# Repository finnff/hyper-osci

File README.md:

# HYPEROSCI

**4 battery-powered, WiFi-synchronized oscilloscopes drawing vector graphics in X/Y mode — for live performance.**

Each of the 4 slave units drives one analog oscilloscope with a stereo audio signal (L = X, R = Y). A central controller (Arduino UNO-Q running Debian) renders osci-render-style vectors as 48 kHz audio and streams it over its own WiFi access point. When the network is gone, every slave falls back within ~6 s to the proven standalone mode: its own microphone drives the scope as an audio-reactive Lissajous visualizer. No laptop on stage, no venue WiFi needed.

## Architecture

```
                     phone browser (web UI, http://192.168.50.1:8080)
                                      │
                                      ▼
        ┌─────────────────────────────────────────────┐
        │        Arduino UNO-Q  (Debian, QRB2210)     │
        │  renderer ─▶ streamer ─▶ WiFi AP (2.4 GHz)  │
        │        SSID HYPEROSCI_AP · 192.168.50.1     │
        └───────┬─────────┬──────────┬─────────┬──────┘
        UDP :5000 audio (unicast ×4) · :5001 sync/cmd · :5002 status
                │         │          │         │
                ▼         ▼          ▼         ▼
          ┌─────────┐ ┌─────────┐ ┌─────────┐ ┌─────────┐
          │ slave 1 │ │ slave 2 │ │ slave 3 │ │ slave 4 │   ESP32-C3 SuperMini
          │         │ │         │ │         │ │         │   + PCM5102A I2S DAC
          │ mic ────┤ │ mic ────┤ │ mic ────┤ │ mic ────┤   + MAX4466 mic (fallback)
          └────┬────┘ └────┬────┘ └────┬────┘ └────┬────┘   + LiPo/TP4056, custom THT carrier PCB
           X/Y ▼       X/Y ▼       X/Y ▼       X/Y ▼
          ┌─────────┐ ┌─────────┐ ┌─────────┐ ┌─────────┐
          │ scope 1 │ │ scope 2 │ │ scope 3 │ │ scope 4 │   analog scopes in X/Y mode
          └─────────┘ └─────────┘ └─────────┘ └─────────┘
```

Sync target ±5 ms via 500 ms beacons; the stream deliberately runs ~450 ms ahead of playback (512 ms slave jitter buffer) to ride out the UNO-Q radio's periodic ~300 ms stalls — latency is irrelevant for scope art, only slave-to-slave sync matters; stream loss > 1 s → automatic local-mic fallback.

## Documentation

**[docs/DESIGN.md](docs/DESIGN.md) is the single source of truth.** Where any other doc disagrees, DESIGN.md wins.

| Doc | What it is |
|-----|------------|
| [docs/DESIGN.md](docs/DESIGN.md) | Canonical decisions: pin map, modules, modes, power, network (LAW) |
| [docs/PLAN.md](docs/PLAN.md) | 5-week execution plan (Jul 17 → Aug 21), critical path, risks, shopping list |
| [docs/protocol.md](docs/protocol.md) | Normative wire protocol (with [src/esp32-slave/include/protocol.h](src/esp32-slave/include/protocol.h)) |
| [docs/hardware/wiring.md](docs/hardware/wiring.md) | Complete hookup guide + bring-up checklist (breadboard now, PCB later) |
| [docs/hardware/pcb.md](docs/hardware/pcb.md) | Carrier PCB: full BOM, power path, layout notes |
| [docs/hardware/power-budget.md](docs/hardware/power-budget.md) | Current draw, battery life, low-battery policy derivation |
| [docs/hardware/bench-capture.md](docs/hardware/bench-capture.md) | Checking slave output without a scope: logic analyzer / spare-MCU capture options, closed agent loop |
| [docs/firmware/esp32-architecture.md](docs/firmware/esp32-architecture.md) | Slave firmware architecture (tasks, drivers, buffers) |
| [docs/osci-render-feature-port-feasibility.md](docs/osci-render-feature-port-feasibility.md) | What else is worth porting from osci-render (fonts, SVG, effects), measured on the board — and the 6 bugs found while looking, all now fixed (§1) |
| [docs/performance-heat-analysis.md](docs/performance-heat-analysis.md) | Why the slave runs hot and why streaming dropped (2026-07-18), with the prioritized fix plan |
| [docs/hardware/pcb-review-findings.md](docs/hardware/pcb-review-findings.md) | 2026-07-26 adversarial design review of the carrier's §4 power path (findings + verdicts) |
| [docs/research/](docs/research/) | Historical planning docs — superseded where they conflict with DESIGN.md |

Research index: [v3.md](docs/research/v3.md) (feasibility) · [v3.1-requirements.md](docs/research/v3.1-requirements.md) (confirmed requirements) · [v3.2-dual-dac.md](docs/research/v3.2-dual-dac.md) (DAC selection) · [UNO-Q_controller.md](docs/research/UNO-Q_controller.md) (controller architecture — note: its whole software stack is illustrative and was NOT built as described: no FastAPI/WebSocket/hostapd, and its 5 GHz AP config is wrong — see DESIGN.md §2 and src/unoq-controller/README.md for what exists) · [esp32-c3-vs-s3.md](docs/research/esp32-c3-vs-s3.md) · [arduino-uno-r4-option.md](docs/research/arduino-uno-r4-option.md) · [README-original.md](docs/research/README-original.md)

## Hardware summary

Per slave (modules socketed on a custom ~70 × 50 mm through-hole carrier PCB — see [docs/hardware/pcb.md](docs/hardware/pcb.md)):

| Module | Role |
|--------|------|
| ESP32-C3 SuperMini | MCU, WiFi, I2S master |
| GY-PCM5102A | 24-bit stereo I2S DAC → scope X/Y via 2× RCA pads (X = L, Y = R), ground-centered DC-coupled |
| MAX4466 | electret mic (on a ~10 cm pigtail) for fallback/hybrid mode |
| TP4056 (USB-C, with protection) + EEMB LP103454 LiPo 3.7 V 2000 mAh | power (~13 h NETWORK / ~30 h LOCAL) |

Scope output is 2× RCA flying-lead pads (X = DAC L, Y = DAC R, series R fitted as 0 Ω links — the DAC module already carries ~470 Ω of its own) driving reused ~50 cm RCA cables into each scope's existing BNC→RCA adapter — no BNC/TRS on our board. Enclosure: 3D-printed case (4× M3 mounts), LiPo mounted off-PCB.

Controls per unit: power switch, mode button (NETWORK / LOCAL / HYBRID), filter-cutoff pot, 2 status LEDs. Controller: 1× Arduino UNO-Q (4 GB, Debian). Pin map and all constants: [src/esp32-slave/include/config.h](src/esp32-slave/include/config.h) — **canonical, do not improvise**.

## Status (2026-07-28)

- [x] Research + feasibility (docs/research/)
- [x] Design locked ([docs/DESIGN.md](docs/DESIGN.md))
- [x] Hardware modules owned/ordered (SuperMinis, DACs, mics, chargers, UNO-Q — arrived, Debian 13 trixie aarch64)
- [x] Slave firmware (`src/esp32-slave/`): full audio/network/mode stack — AsyncUDP audio RX, 512 ms jitter buffer + concealment, local mic/pattern renderers, console; unit #1 on breadboard streams end-to-end
- [x] UNO-Q controller app **deployed** (`hyperosci-controller` systemd service): streamer + web UI + patterns/Hershey-font text (accents composed from the face's own strokes)/effects/presets — [src/unoq-controller/README.md](src/unoq-controller/README.md). osci-render was built for aarch64 but deliberately **not** integrated (no headless entry point — [docs/text-rendering-findings.md](docs/text-rendering-findings.md))
- [x] Six controller bugs found by the feature-port study fixed and deployed 2026-07-22, including the one that had the daemon beaconing out of the USB tether instead of the AP — slave 121 now receives audio ([docs/…feasibility.md §1](docs/osci-render-feature-port-feasibility.md))
- [x] Boots unattended 2026-07-22: `hyperosci-ap` now autoconnects (it never did — that, not the controller, was the real "no slaves discovered yet…"), the USB tether holds a fixed `10.42.0.5` alongside DHCP, and the dashboard names the AP-down case instead of showing an empty list. Cold boot to streaming: 18 s ([src/unoq-controller/STATUS.md](src/unoq-controller/STATUS.md))
- [x] Survives a power cut with no laptop 2026-07-22: the live pattern persists to `~/hype_state.json` and is restored before the first audio block, presets keep one generation of undo, and a root `hyperosci-netwatch` timer re-ups the AP (and bounces it on the documented ath10k wedge). Regression checks in [src/unoq-controller/tests/](src/unoq-controller/tests/) — run them **on the board**
- [x] Carrier PCB designed & **ordered 2026-07-28** — JLCPCB, qty 10, DHL Express (DDP), $45.42 landed, arriving **Aug 5–7** (order gate was ~Aug 1; met three days early — see [docs/PLAN.md](docs/PLAN.md)). ⏳ Production is paused until the production file is confirmed by email. **Routed and gate-clean as of 2026-07-28** — the pre-fab DFM pass moved copper and killed router seed 11; a 16-variant re-sweep found exactly one clean result (**seed 33**, now the default) and the board is 1343 segments / 48 GND vias / 0 unconnected / 0 DRC violations, with the width tables regenerated from the routed copper. **Nothing gates the plot any more:** SW1 was the last item and it closed 2026-07-28 off the SS12D00 drawing — 2.5 mm pitch (neither value the footprint was drawn for, and 0.05 mm off the centre of the slot's window), body 8.5 × 3.7 mm on the pin centreline, no layout change. **The fab package is plotted and committed** to [`hw/carrier/fab/`](hw/carrier/fab/); `tools/plot_fab.py` regenerates it and refuses to write the zip unless the board still passes. Detail: [`hw/carrier/layout-notes.md`](hw/carrier/layout-notes.md)
- [ ] 4-slave sync demo (slaves 2–4 not yet on breadboards; 3 built slaves need reflashing for the lost-packets counter)
- [ ] Assembly + venue rehearsal (show 2026-08-21)

## Repository layout

```
docs/                 all documentation (DESIGN.md = canon)
  research/           original v3 planning docs (historical)
  hardware/           wiring, power budget, PCB
  firmware/           firmware architecture
  protocol.md         normative wire protocol
  PLAN.md             5-week execution plan
src/esp32-slave/      PlatformIO project — slave firmware
src/unoq-controller/  UNO-Q controller app (streamer + renderer + web UI, deployed)
hw/carrier/           KiCad carrier PCB — generated end-to-end by tools/*.py
```

The repo root also carries two gitignored third-party binaries: `arduino-flasher-cli` (UNO-Q Debian flasher) and `osci-render-premium-linux.zip` (x86-64 only — does not run on the aarch64 UNO-Q; kept for desktop reference. The controller renders natively instead, see [docs/text-rendering-findings.md](docs/text-rendering-findings.md)).

## Quickstart

Slave firmware build/flash instructions: **[src/esp32-slave/README.md](src/esp32-slave/README.md)** (PlatformIO + pioarduino platform, USB-C CDC console).

One rule worth repeating from DESIGN.md §9: **during breadboard bring-up, never plug in USB-C while the battery power switch is ON** — SuperMini clones tie VBUS to the 5 V pin (meter-confirmed 2026-07-18) and would back-feed the battery. Flash with the switch OFF. The carrier PCB's load-sharing power path is *intended* to remove this rule, but design review (2026-07-26) found the SuperMini-side detection unreliable against a sagging laptop port — so treat the rule as permanent until `docs/hardware/pcb.md` §4.4 passes on an assembled board.

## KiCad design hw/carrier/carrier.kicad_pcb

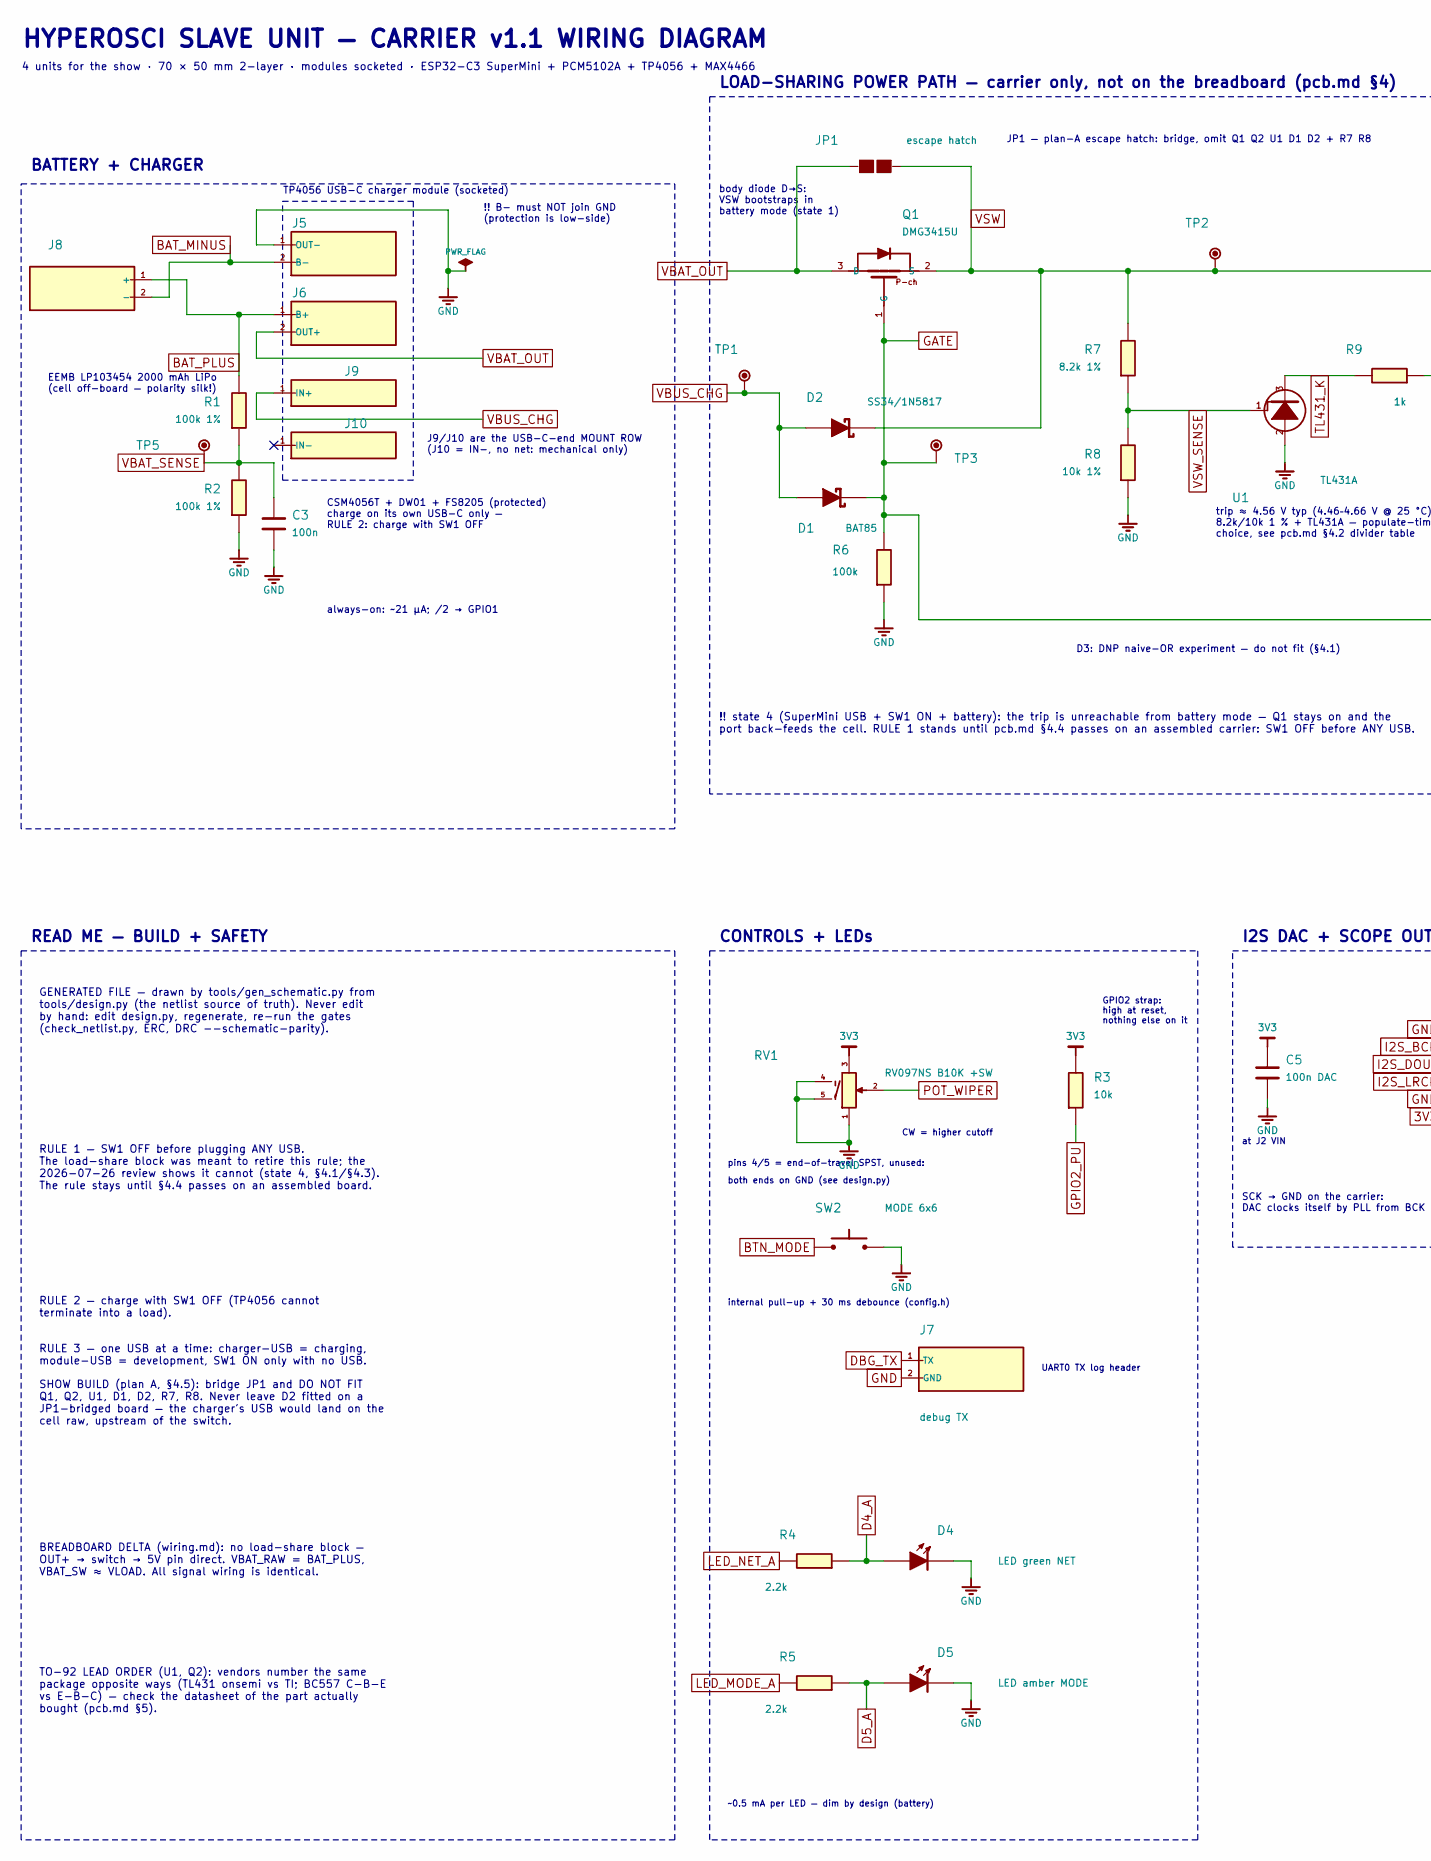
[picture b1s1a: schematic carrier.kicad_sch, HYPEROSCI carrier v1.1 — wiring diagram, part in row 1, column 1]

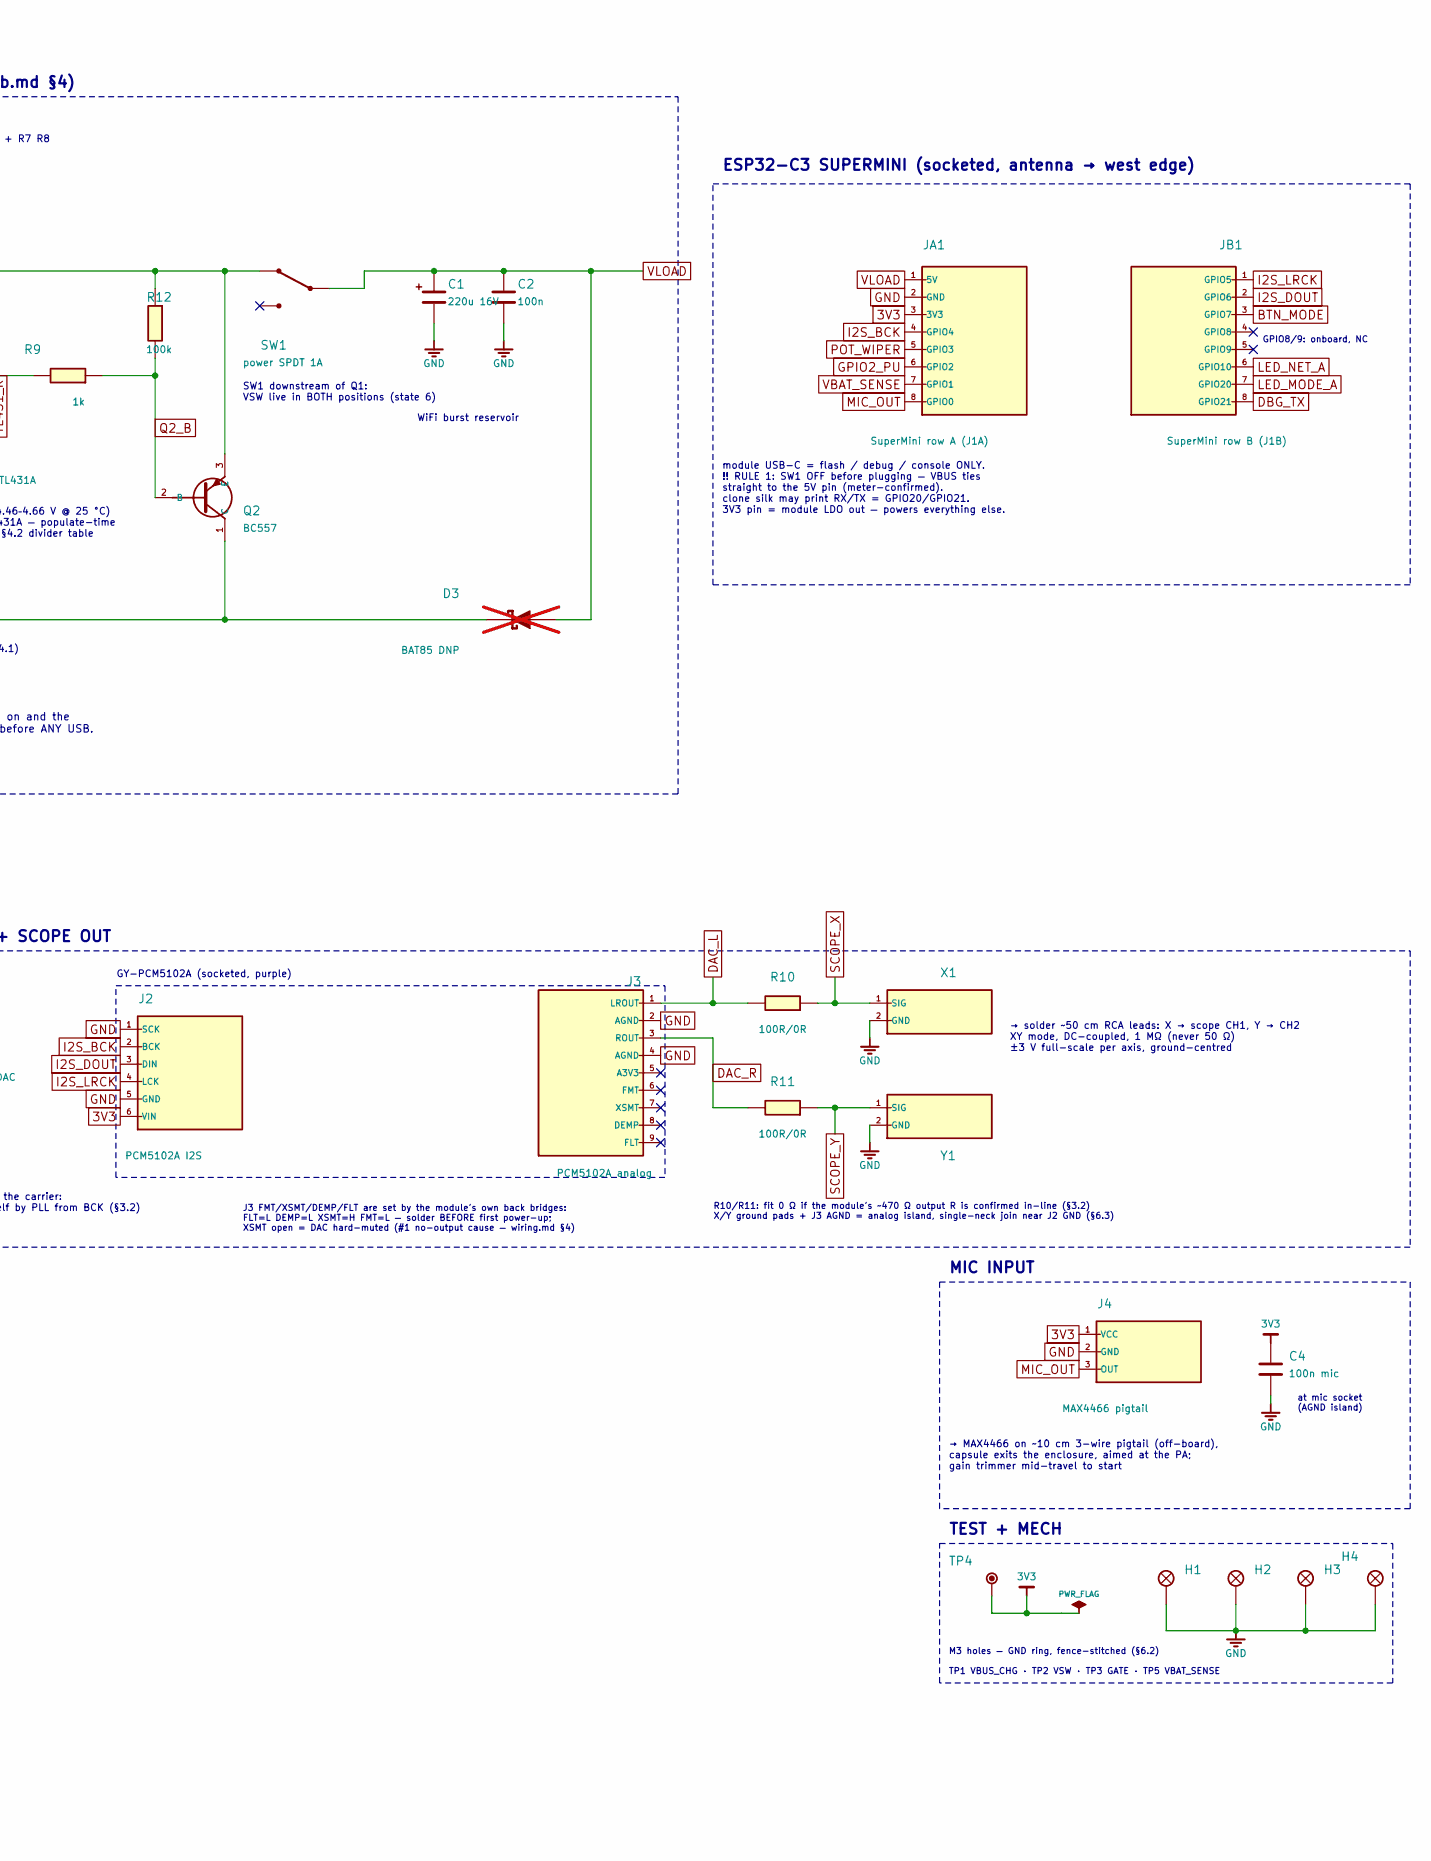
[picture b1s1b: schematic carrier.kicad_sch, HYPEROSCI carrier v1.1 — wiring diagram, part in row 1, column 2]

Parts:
C1: 220u 16V; CP_Radial_D6.3mm_P2.50mm
C2, C3: 100n; C_Disc_D5.0mm_W2.5mm_P2.50mm
C4: 100n mic; C_Disc_D5.0mm_W2.5mm_P2.50mm
C5: 100n DAC; C_Disc_D5.0mm_W2.5mm_P2.50mm
D1: BAT85; D_DO-35_SOD27_P7.62mm_Horizontal
D2: SS34/1N5817; D_Dual_SMA_DO41
D3: BAT85 DNP; D_DO-35_SOD27_P7.62mm_Horizontal; not fitted
D4: LED green NET; LED_D3.0mm
D5: LED amber MODE; LED_D3.0mm
H1, H2, H3, H4: M3; MountingHole_3.2mm_M3_Pad
J2: PCM5102A I2S; PinSocket_1x06_P2.54mm_Vertical
J3: PCM5102A analog; PinSocket_1x09_P2.54mm_Vertical
J4: MAX4466 pigtail; PinSocket_1x03_P2.54mm_Vertical
J5: TP4056 OUT-/B-; TP4056_Pads_OUTminus_Bminus
J6: TP4056 B+/OUT+; TP4056_Pads_Bplus_OUTplus
J7: debug TX; PinHeader_1x02_P2.54mm_Vertical
J8: LiPo JST-PH; JST_PH_S2B-PH-K_1x02_P2.00mm_Horizontal
J9: TP4056 IN+ / mount (J6b); TP4056_MountPin
J10: TP4056 IN- / mount; TP4056_MountPin
JA1: SuperMini row A (J1A); PinSocket_1x08_P2.54mm_Vertical
JB1: SuperMini row B (J1B); PinSocket_1x08_P2.54mm_Vertical
JP1: escape hatch; SolderJumper_P2.54
Q1: DMG3415U; SOT-23_Handsoldering
Q2: BC557; TO-92_Inline_Wide
R1, R2: 100k 1%; R_Axial_DIN0207_L6.3mm_D2.5mm_P2.54mm_Vertical
R3: 10k; R_Axial_DIN0207_L6.3mm_D2.5mm_P10.16mm_Horizontal
R4, R5: 2.2k; R_Axial_DIN0207_L6.3mm_D2.5mm_P2.54mm_Vertical
R6, R12: 100k; R_Axial_DIN0207_L6.3mm_D2.5mm_P2.54mm_Vertical
R7: 8.2k 1%; R_Axial_DIN0207_L6.3mm_D2.5mm_P2.54mm_Vertical
R8: 10k 1%; R_Axial_DIN0207_L6.3mm_D2.5mm_P2.54mm_Vertical
R9: 1k; R_Axial_DIN0207_L6.3mm_D2.5mm_P2.54mm_Vertical
R10, R11: 100R/0R; R_Axial_DIN0207_L6.3mm_D2.5mm_P2.54mm_Vertical
RV1: RV097NS B10K +SW; RV097NS_Horizontal_Switch
SW1: power SPDT 1A; SW_Slide_SPDT_DualPitch
SW2: MODE 6x6; SW_PUSH_6mm_H5mm
TP1: VBUS_CHG; TestPoint_Pad_D1.5mm
TP2: VSW; TestPoint_Pad_D1.5mm
TP3: GATE; TestPoint_Pad_D1.5mm
TP4: 3V3; TestPoint_Pad_D1.5mm
TP5: VBAT_SENSE; TestPoint_Pad_D1.5mm
U1: TL431A; TO-92_Inline_Wide
X1: scope X RCA pads; RCA_FlyingLead_Pads
Y1: scope Y RCA pads; RCA_FlyingLead_Pads

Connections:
3V3: C4.1, C5.1, J2.6 (VIN), J4.1 (VCC), JA1.3 (3V3), R3.1, RV1.3 (CW), TP4.1
BAT_MINUS: J5.2 (B-), J8.2 (-)
BAT_PLUS: J6.1 (B+), J8.1 (+), R1.1
BTN_MODE: JB1.3 (GPIO7), SW2.1
D4_A: D4.2 (A), R4.2
D5_A: D5.2 (A), R5.2
DAC_L: J3.1 (LROUT), R10.1
DAC_R: J3.3 (ROUT), R11.1
DBG_TX: J7.1 (TX), JB1.8 (GPIO21)
GATE: D1.1 (K), D3.1 (K), Q1.1 (G), Q2.1 (C), R6.1, TP3.1
GND: C1.2 (-), C2.2, C3.2, C4.2, C5.2, D4.1 (K), D5.1 (K), H1.1, H2.1, H3.1, H4.1, J2.1 (SCK), J2.5 (GND), J3.2 (AGND), J3.4 (AGND), J4.2 (GND), J5.1 (OUT-), J7.2 (GND), JA1.2 (GND), R2.2, R6.2, R8.2, RV1.1 (CCW), RV1.4 (S1), RV1.5 (S2), SW2.2, U1.2 (A), X1.2 (GND), Y1.2 (GND)
GPIO2_PU: JA1.6 (GPIO2), R3.2
I2S_BCK: J2.2 (BCK), JA1.4 (GPIO4)
I2S_DOUT: J2.3 (DIN), JB1.2 (GPIO6)
I2S_LRCK: J2.4 (LCK), JB1.1 (GPIO5)
LED_MODE_A: JB1.7 (GPIO20), R5.1
LED_NET_A: JB1.6 (GPIO10), R4.1
MIC_OUT: J4.3 (OUT), JA1.8 (GPIO0)
POT_WIPER: JA1.5 (GPIO3), RV1.2 (W)
Q2_B: Q2.2 (B), R9.2, R12.1
SCOPE_X: R10.2, X1.1 (SIG)
SCOPE_Y: R11.2, Y1.1 (SIG)
TL431_K: R9.1, U1.3 (K)
VBAT_OUT: J6.2 (OUT+), JP1.1, Q1.3 (D)
VBAT_SENSE: C3.1, JA1.7 (GPIO1), R1.2, R2.1, TP5.1
VBUS_CHG: D1.2 (A), D2.2 (A), J9.1, TP1.1
VLOAD: C1.1 (+), C2.1, D3.2 (A), JA1.1 (5V), SW1.2 (COM)
VSW: D2.1 (K), JP1.2, Q1.2 (S), Q2.3 (E), R7.1, R12.2, SW1.1 (A), TP2.1
VSW_SENSE: R7.2, R8.1, U1.1 (REF)

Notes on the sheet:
BATTERY + CHARGER
TP4056 USB-C charger module (socketed)
J9/J10 are the USB-C-end MOUNT ROW (J10 = IN-, no net: mechanical only)
CSM4056T + DW01 + FS8205 (protected) charge on its own USB-C only — RULE 2: charge with SW1 OFF
EEMB LP103454 2000 mAh LiPo (cell off-board — polarity silk!)
!! B− must NOT join GND (protection is low-side)
always-on: ~21 µA; /2 → GPIO1
LOAD-SHARING POWER PATH — carrier only, not on the breadboard (pcb.md §4)
JP1 — plan-A escape hatch: bridge, omit Q1 Q2 U1 D1 D2 + R7 R8
body diode D→S: VSW bootstraps in battery mode (state 1)
trip ≈ 4.56 V typ (4.46–4.66 V @ 25 °C) 8.2k/10k 1 % + TL431A — populate-time choice, see pcb.md §4.2 divider table
SW1 downstream of Q1: VSW live in BOTH positions (state 6)
WiFi burst reservoir
D3: DNP naive-OR experiment — do not fit (§4.1)
!! state 4 (SuperMini USB + SW1 ON + battery): the trip is unreachable from battery mode — Q1 stays on and the port back-feeds the cell. RULE 1 stands until pcb.md §4.4 passes on an assembled carrier: SW1 OFF before ANY USB.
ESP32-C3 SUPERMINI (socketed, antenna → west edge)
GPIO8/9: onboard, NC
module USB-C = flash / debug / console ONLY. !! RULE 1: SW1 OFF before plugging — VBUS ties straight to the 5V pin (meter-confirmed). clone silk may print RX/TX = GPIO20/GPIO21. 3V3 pin = module LDO out — powers everything else.
I2S DAC + SCOPE OUT
GY-PCM5102A (socketed, purple)
SCK → GND on the carrier: DAC clocks itself by PLL from BCK (§3.2)
J3 FMT/XSMT/DEMP/FLT are set by the module's own back bridges: FLT=L DEMP=L XSMT=H FMT=L — solder BEFORE first power-up; XSMT open = DAC hard-muted (#1 no-output cause — wiring.md §4)
→ solder ~50 cm RCA leads: X → scope CH1, Y → CH2 XY mode, DC-coupled, 1 MΩ (never 50 Ω) ±3 V full-scale per axis, ground-centred
R10/R11: fit 0 Ω if the module's ~470 Ω output R is confirmed in-line (§3.2) X/Y ground pads + J3 AGND = analog island, single-neck join near J2 GND (§6.3)
at J2 VIN
MIC INPUT
→ MAX4466 on ~10 cm 3-wire pigtail (off-board), capsule exits the enclosure, aimed at the PA; gain trimmer mid-travel to start
at mic socket (AGND island)
CONTROLS + LEDs
CW = higher cutoff
pins 4/5 = end-of-travel SPST, unused:
both ends on GND (see design.py)
internal pull-up + 30 ms debounce (config.h)
GPIO2 strap: high at reset, nothing else on it
UART0 TX log header
~0.5 mA per LED — dim by design (battery)
TEST + MECH
M3 holes — GND ring, fence-stitched (§6.2)
TP1 VBUS_CHG · TP2 VSW · TP3 GATE · TP5 VBAT_SENSE
READ ME — BUILD + SAFETY

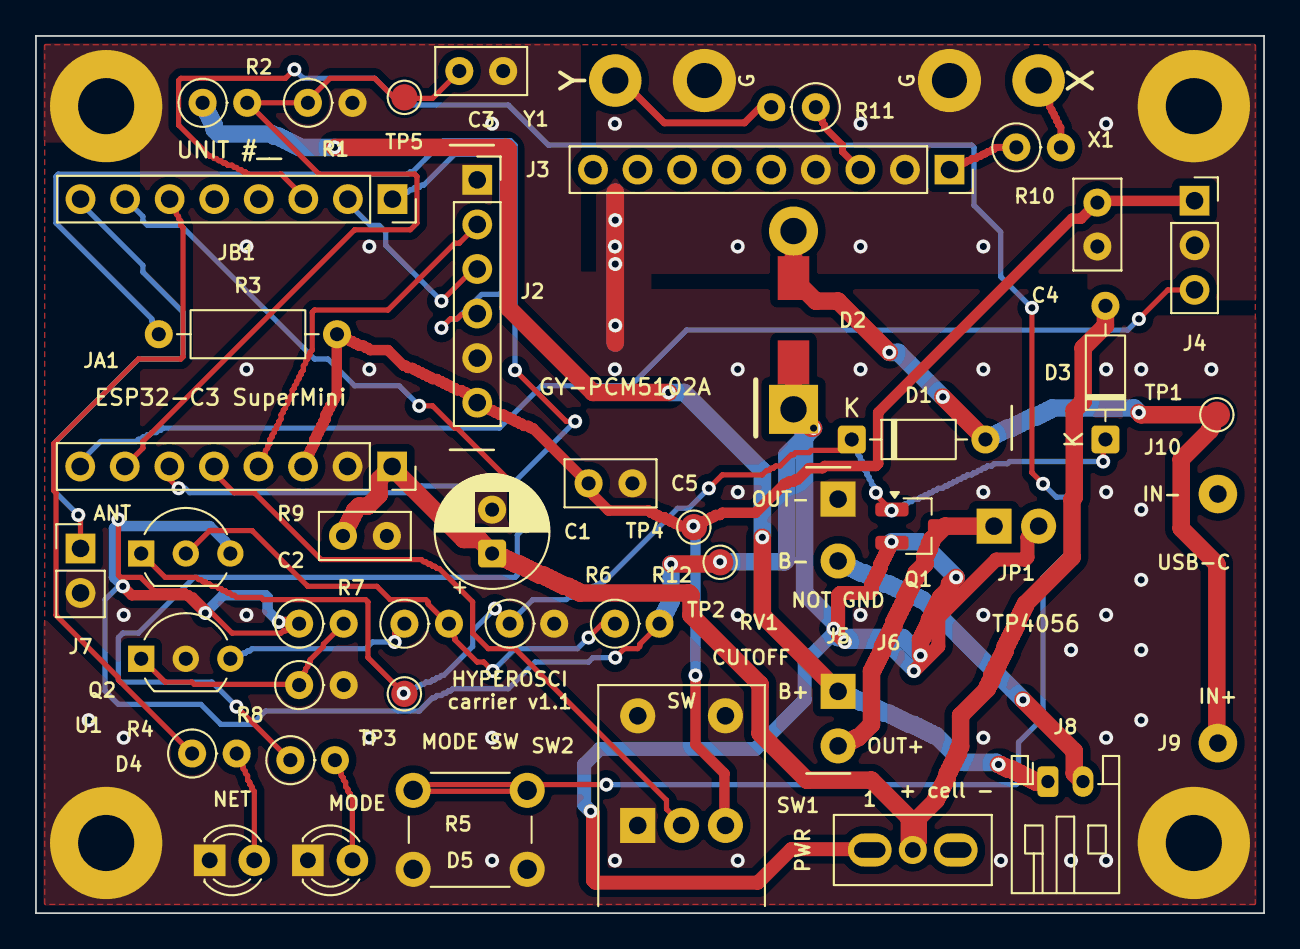
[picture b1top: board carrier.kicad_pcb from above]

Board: 2 copper layers, 70.0 x 50.0 mm, 51 parts (0 on the bottom side), 29 nets.

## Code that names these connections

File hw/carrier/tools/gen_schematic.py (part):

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    defsym("X_" + ref, pins, gfx, hide_nums=False, hide_names=False,
           name_size=0.9, num_size=0.8)

defconn("JA1", ["5V", "GND", "3V3", "GPIO4", "GPIO3", "GPIO2", "GPIO1",
                "GPIO0"], "left")
defconn("JB1", ["GPIO5", "GPIO6", "GPIO7", "GPIO8", "GPIO9", "GPIO10",
                "GPIO20", "GPIO21"], "right")
defconn("J2", ["SCK", "BCK", "DIN", "LCK", "GND", "VIN"], "left")
defconn("J3", ["LROUT", "AGND", "ROUT", "AGND", "A3V3", "FMT", "XSMT",
               "DEMP", "FLT"], "right")
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PS("GND", 34, 68)
W("GND", ("C3", 2), (38, 70))
PS("GND", 38, 70)
T("always-on: ~21 µA; /2 → GPIO1", 44, 75, 1.0)

# ===========================================================================
# BLOCK B — load-sharing power path (top-middle)
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  (184, 36), ("SW1", 1), w=0.3556)
W("VSW", ("JP1", 2), (118, 24), (118, 36))
L("VSW", 118, 30)
# VBUS_CHG spine feeding D2 (to VSW) and D1 (to GATE)
W("VBUS_CHG", (90, 50), ("TP1", 1), (96, 50), (96, 54), ("D2", 2))
L("VBUS_CHG", 90, 50, 180)
W("VBUS_CHG", (96, 54), (96, 62), ("D1", 2))
W("VSW", ("D2", 1), (126, 54), (126, 36))
# GATE spine
W("GATE", ("Q1", 1), (108, 44), (108, 58), (108, 62), (108, 64), ("R6", 1))
W("GATE", (108, 44), (112, 44))
L("GATE", 112, 44)
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for pnum in (1, 2, 3, 6, 7, 8):
    LP("JB1", pnum, 0)
T("GPIO8/9: onboard, NC", 303, 44, 0.9)
T("module USB-C = flash / debug / console ONLY.\n!! RULE 1: SW1 OFF before plugging — VBUS ties\nstraight to the 5V pin (meter-confirmed).\nclone silk may print RX/TX = GPIO20/GPIO21.\n3V3 pin = module LDO out — powers everything else.", 241, 61, 1.0)

# ===========================================================================
# BLOCK D — DAC + scope out (bottom-middle)
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
place("R3", 130, 130, refpos=(132, 128.5, "left"), valpos=(132, 130.5, "left"))
PS("P3V3", 130, 126)
W("GPIO2_PU", ("R3", 2), (130, 136))
L("GPIO2_PU", 130, 136, 270)
T("GPIO2 strap:\nhigh at reset,\nnothing else on it", 133, 121, 0.9)

place("J7", 116, 162, refpos=(112, 157.5, "left"), valpos=(112, 167.5, "left"))
LP("J7", 1, 180)
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T("RULE 2 — charge with SW1 OFF (TP4056 cannot\nterminate into a load).", 11, 155, 1.1)
T("RULE 3 — one USB at a time: charger-USB = charging,\nmodule-USB = development, SW1 ON only with no USB.", 11, 160.5, 1.1)
T("SHOW BUILD (plan A, §4.5): bridge JP1 and DO NOT FIT\nQ1, Q2, U1, D1, D2, R7, R8. Never leave D2 fitted on a\nJP1-bridged board — the charger's USB would land on the\ncell raw, upstream of the switch.", 11, 166, 1.1)
T("BREADBOARD DELTA (wiring.md): no load-share block —\nOUT+ → switch → 5V pin direct. VBAT_RAW = BAT_PLUS,\nVBAT_SW ≈ VLOAD. All signal wiring is identical.", 11, 184, 1.1)
T("TO-92 LEAD ORDER (U1, Q2): vendors number the same\npackage opposite ways (TL431 onsemi vs TI; BC557 C-B-E\nvs E-B-C) — check the datasheet of the part actually\nbought (pcb.md §5).", 11, 199, 1.1)

T("HYPEROSCI SLAVE UNIT — CARRIER v1.1 WIRING DIAGRAM", 9, 9.5, 2.5, True)
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
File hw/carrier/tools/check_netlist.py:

#!/usr/bin/env python3
"""Verify the exported KiCad netlist against design.py AND config.h.

This is the respin-prevention gate: it re-parses what KiCad actually
understood (not what we intended to emit) and checks:
  1. every design.py pin/net pair survived into the netlist, and nothing extra
  2. the SuperMini socket nets match config.h's PIN_* GPIO assignments
  3. the §2 socket table invariants (strapping pins NC, SCK tied to GND, ...)

Run from hw/carrier/:
  kicad-cli sch export netlist -o /tmp/carrier.net carrier.kicad_sch
  python3 tools/check_netlist.py /tmp/carrier.net
"""
import os, re, sys
sys.path.insert(0, os.path.dirname(__file__))
from design import COMPONENTS, norm

# ---- tiny s-expression parser ----------------------------------------------
def parse(text):
    toks = re.findall(r'"(?:[^"\\]|\\.)*"|\(|\)|[^\s()]+', text)
    def rd(i):
        assert toks[i] == "(", toks[i]
        out = []
        i += 1
        while toks[i] != ")":
            if toks[i] == "(":
                node, i = rd(i)
                out.append(node)
            else:
                t = toks[i]
                out.append(t[1:-1] if t.startswith('"') else t)
                i += 1
        return out, i + 1
    return rd(0)[0]

def find_all(node, tag):
    return [n for n in node if isinstance(n, list) and n and n[0] == tag]

netfile = sys.argv[1]
root = parse(open(netfile).read())
nets_sec = find_all(root, "nets")[0]

# netlist -> {(ref, pin): netname}
got = {}
netnames = {}
for net in find_all(nets_sec, "net"):
    name = next(n[1] for n in net if isinstance(n, list) and n[0] == "name")
    for node in find_all(net, "node"):
        ref = next(n[1] for n in node if isinstance(n, list) and n[0] == "ref")
        pin = next(n[1] for n in node if isinstance(n, list) and n[0] == "pin")
        if name.startswith("unconnected-("):
            continue          # KiCad's synthetic net for a no-connect marker
        got[(ref, pin)] = name
        netnames.setdefault(name, []).append(f"{ref}.{pin}")

errors = []

# ---- 1. design.py <-> netlist, both directions ------------------------------
want = {}
for ref, c in COMPONENTS.items():
    for pad, net in norm(c)[3].items():
        want[(ref, pad)] = net

for (ref, pad), net in want.items():
    if net is None:
        if (ref, pad) in got:
            errors.append(f"{ref}.{pad}: design says NC, netlist has '{got[(ref, pad)]}'")
    else:
        g = got.get((ref, pad))
        if g != net:
            errors.append(f"{ref}.{pad}: design says '{net}', netlist has '{g}'")
extra = set(got) - {k for k, v in want.items() if v is not None}
for ref, pad in sorted(extra):
    errors.append(f"{ref}.{pad}: in netlist ('{got[(ref, pad)]}') but not in design.py")

# ---- 2. config.h GPIO map <-> SuperMini socket nets -------------------------
cfg = open(os.path.join(os.path.dirname(__file__),
           "..", "..", "..", "src", "esp32-slave", "include", "config.h")).read()
def cpin(name):
    return int(re.search(rf"#define\s+{name}\s+(\d+)", cfg).group(1))

# socket position -> GPIO (pcb.md §2, TENSTAR silk confirmed measurements.md)
J1A_GPIO = {"4": 4, "5": 3, "6": 2, "7": 1, "8": 0}          # pins 1-3 = 5V/GND/3V3
J1B_GPIO = {"1": 5, "2": 6, "3": 7, "4": 8, "5": 9, "6": 10, "7": 20, "8": 21}

expect_gpio_net = {
    cpin("PIN_MIC_ADC"): "MIC_OUT",
    cpin("PIN_VBAT_ADC"): "VBAT_SENSE",
    cpin("PIN_POT_ADC"): "POT_WIPER",
    cpin("PIN_I2S_BCK"): "I2S_BCK",
    cpin("PIN_I2S_LRCK"): "I2S_LRCK",
    cpin("PIN_I2S_DOUT"): "I2S_DOUT",
    cpin("PIN_BTN_MODE"): "BTN_MODE",
    cpin("PIN_LED_ONBOARD"): None,      # GPIO8: onboard LED, must be NC
    cpin("PIN_BTN_BOOT"): None,         # GPIO9: BOOT, must be NC
    cpin("PIN_LED_NET"): "LED_NET_A",
    cpin("PIN_LED_MODE"): "LED_MODE_A",
    2: "GPIO2_PU",                      # strapping pull-up (DESIGN §4)
    21: "DBG_TX",
}
for row, gmap in (("JA1", J1A_GPIO), ("JB1", J1B_GPIO)):
    for pad, gpio in gmap.items():
        exp = expect_gpio_net.get(gpio, "?unmapped?")
        act = got.get((row, pad))
        if exp != act:
            errors.append(f"GPIO{gpio} ({row}.{pad}): config.h expects "
                          f"'{exp}', netlist has '{act}'")

# ---- 3. §2/§3 invariants ----------------------------------------------------
inv = [
    (("J2", "1"), "GND", "PCM5102A SCK must be tied to GND (PLL from BCK)"),
    (("J5", "2"), "BAT_MINUS", "B- must NOT be GND (DW01 low-side protection)"),
    (("J8", "2"), "BAT_MINUS", "JST B- must go to J5 B- only"),
    (("SW1", "2"), "VLOAD", "power switch COM feeds the load"),
    (("Q1", "3"), "VBAT_OUT", "P-FET drain at battery side"),
    (("D3", "2"), "VLOAD", "DNP naive-OR diode senses the load node (§4.2)"),
]
for key, expnet, why in inv:
    if got.get(key) != expnet:
        errors.append(f"invariant: {key[0]}.{key[1]} should be '{expnet}' ({why})")
if "BAT_MINUS" in netnames and \
        sorted(netnames["BAT_MINUS"]) != ["J5.2", "J8.2"]:
    errors.append(f"BAT_MINUS must be exactly J5.2+J8.2, got {sorted(netnames['BAT_MINUS'])}")

# ---- report -----------------------------------------------------------------
print(f"netlist: {len(netnames)} nets, {len(got)} connected pins; "
      f"design: {sum(1 for v in want.values() if v)} connected pins")
for name in sorted(netnames):
    print(f"  {name:12s} {' '.join(sorted(netnames[name]))}")
if errors:
    print(f"\nFAIL — {len(errors)} problems:")
    for e in errors:
        print("  !!", e)
    sys.exit(1)
print("\nOK — netlist matches design.py, config.h GPIO map, and §2/§3 invariants")
